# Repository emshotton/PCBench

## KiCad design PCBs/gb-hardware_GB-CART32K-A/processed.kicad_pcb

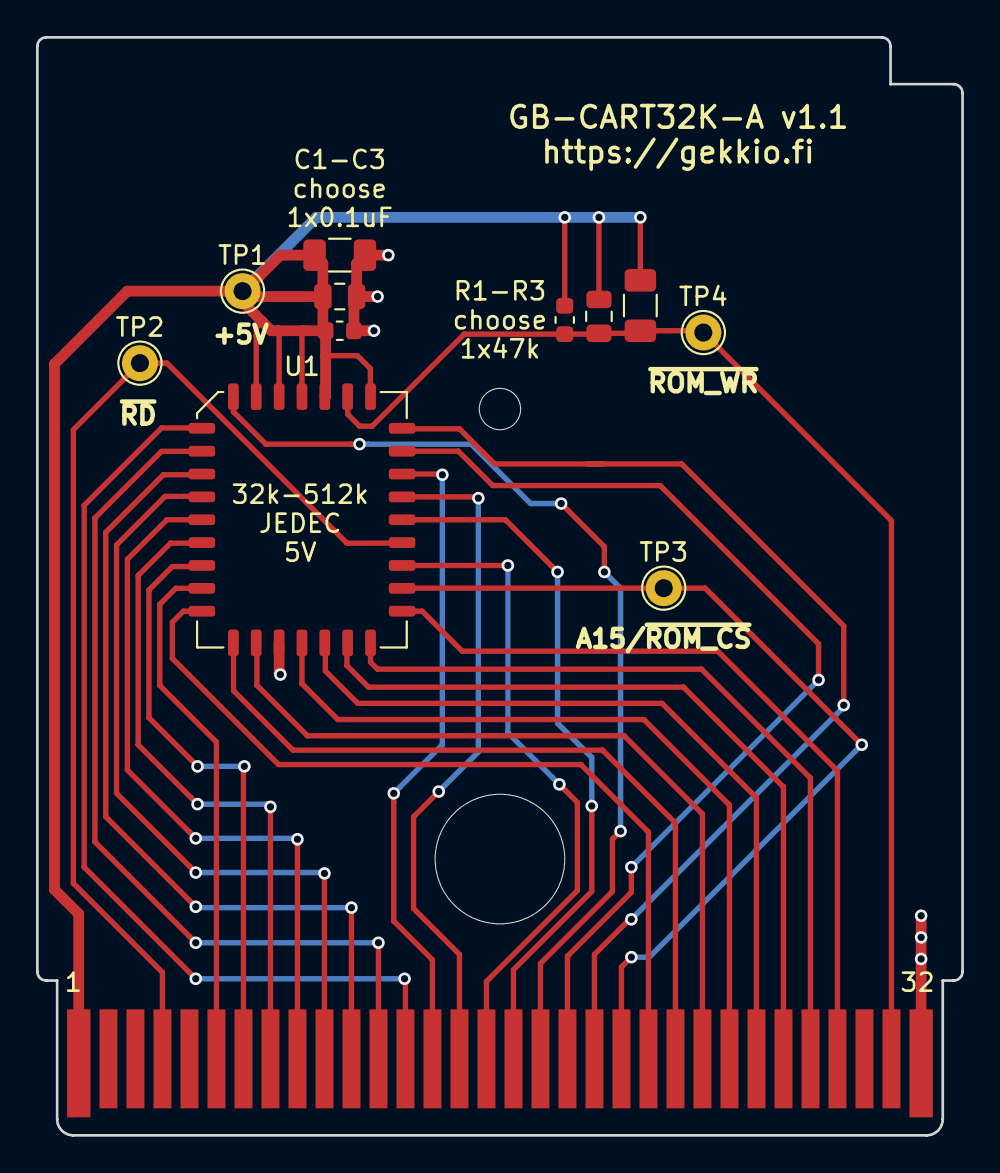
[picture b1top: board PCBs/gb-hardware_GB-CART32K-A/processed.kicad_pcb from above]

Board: 2 copper layers, 51.4 x 61.0 mm, 14 parts (0 on the bottom side), 28 nets.

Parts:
C1: 0.1uF; C_0603_1608Metric
C2: 1uF; C_0805_2012Metric
C3: 10uF; C_1206_3216Metric
H1: DNF; MountingHole_7.2mm
H2: DNF; MountingHole_2.3mm
J1: DNF; GameBoy_Cartridge_1x32_P1.50mm_Edge
R1: 47k; R_0603_1608Metric
R2: 47k; R_0805_2012Metric
R3: 47k; R_1206_3216Metric
TP1, TP2, TP3, TP4: TestPoint; TestPoint_THTPad_D2.0mm_Drill1.0mm
U1: SST39SF040; PLCC-32_11.4x14.0mm_P1.27mm

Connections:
+5V: C1.1, C2.1, C3.1, J1.1, R1.1, R2.1, R3.1, TP1.1, U1.1, U1.2, U1.3, U1.30, U1.32
/A0: J1.6, U1.12
/A1: J1.7, U1.11
/A2: J1.8, U1.10
/A3: J1.9, U1.9
/A4: J1.10, U1.8
/A5: J1.11, U1.7
/A6: J1.12, U1.6
/A7: J1.13, U1.5
/A8: J1.14, U1.27
/A9: J1.15, U1.26
/A10: J1.16, U1.23
/A11: J1.17, U1.25
/A12: J1.18, U1.4
/A13: J1.19, U1.28
/A14: J1.20, U1.29
/D0: J1.22, U1.13
/D1: J1.23, U1.14
/D2: J1.24, U1.15
/D3: J1.25, U1.17
/D4: J1.26, U1.18
/D5: J1.27, U1.19
/D6: J1.28, U1.20
/D7: J1.29, U1.21
/~RD: J1.4, TP2.1, U1.24
/~ROM_CS: J1.21, TP3.1, U1.22
/~ROM_WR: J1.31, R1.2, R2.2, R3.2, TP4.1, U1.31
GND: C1.2, C2.2, C3.2, J1.32, U1.16

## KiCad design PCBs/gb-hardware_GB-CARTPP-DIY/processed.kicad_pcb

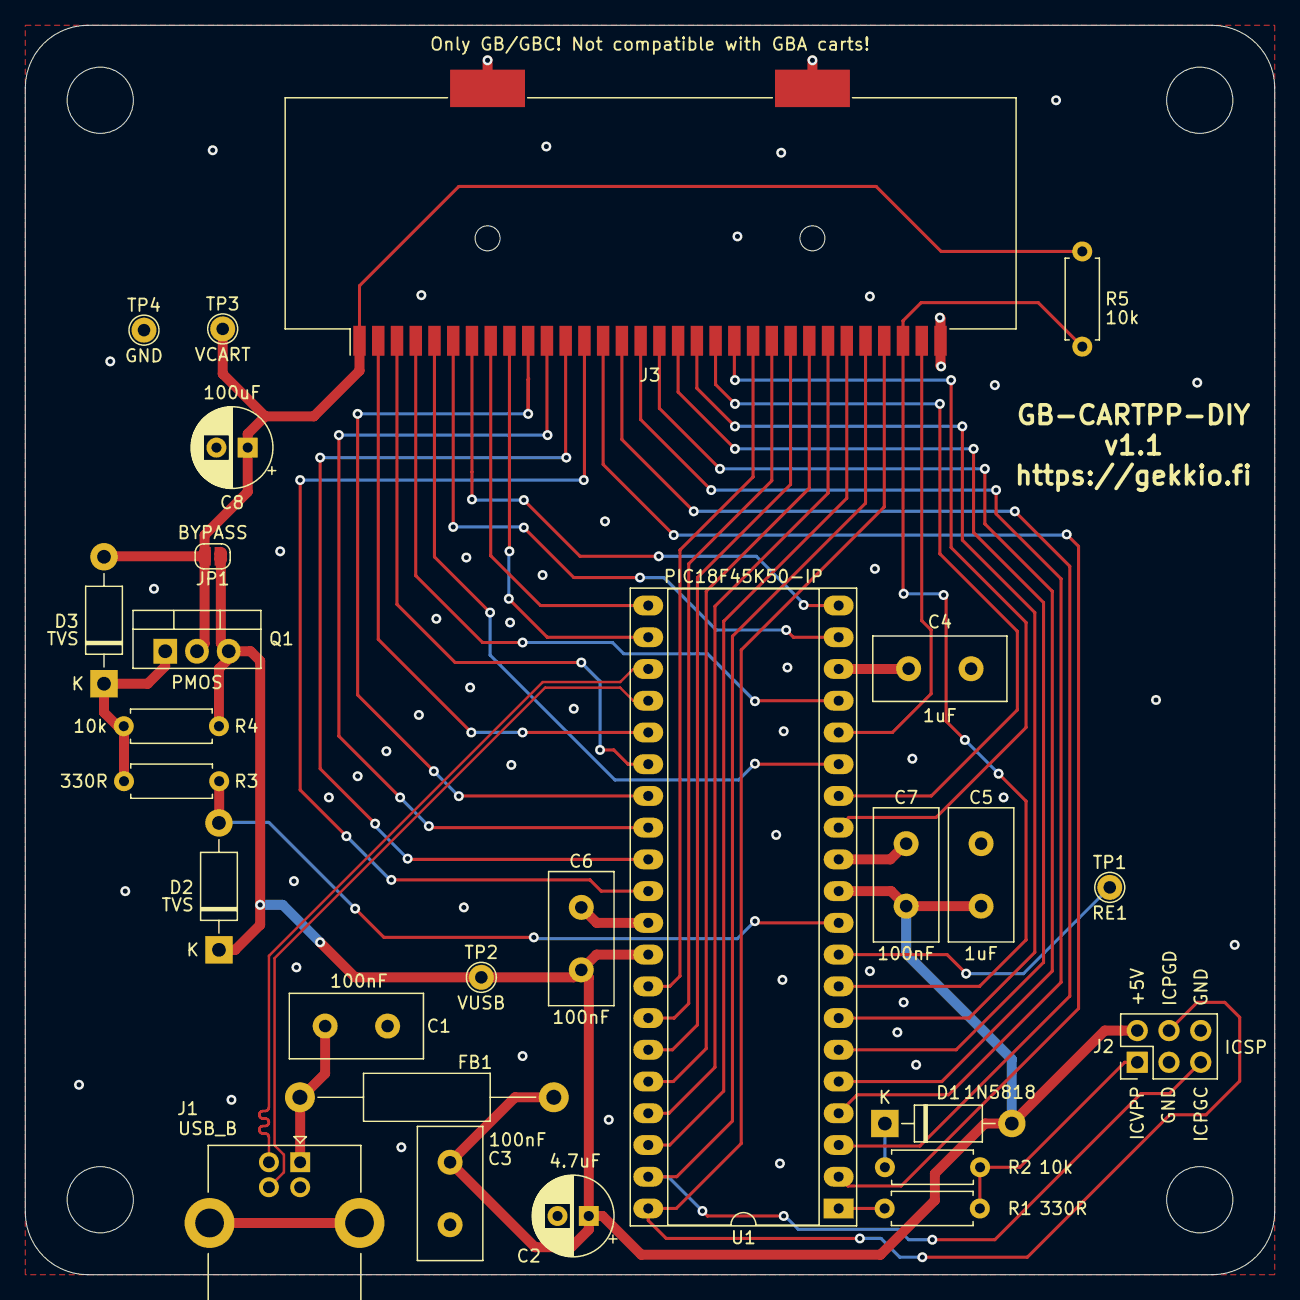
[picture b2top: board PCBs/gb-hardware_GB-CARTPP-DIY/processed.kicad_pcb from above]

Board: 2 copper layers, 100.0 x 100.0 mm, 31 parts (0 on the bottom side), 43 nets.

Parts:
C1, C3, C6, C7: 100nF; C_Disc_D10.5mm_W5.0mm_P5.00mm
C2: 4.7uF; CP_Radial_D6.3mm_P2.50mm
C4, C5: 1uF; C_Disc_D10.5mm_W5.0mm_P5.00mm
C8: 100uF; CP_Radial_D6.3mm_P2.50mm
D1: 1N5818; D_DO-41_SOD81_P10.16mm_Horizontal
D2, D3: TVS; D_DO-41_SOD81_P10.16mm_Horizontal
FB1: Ferrite_Bead_Small; R_Axial_DIN0411_L9.9mm_D3.6mm_P20.32mm_Horizontal
H1, H2, H3, H4: DNP; MountingHole_5.3mm_M5
J1: USB_B; USB_B_Lumberg_2411_02_Horizontal
J2: ICSP; PinHeader_2x03_P2.54mm_Vertical
J3: GameBoy_Cartridge_MountingPin; GameBoy_Cartridge_AGS_1x32-1MP_P1.50mm_Socket_Horizontal
JP1: BYPASS; SolderJumper-2_P1.3mm_Open_RoundedPad1.0x1.5mm
Q1: PMOS; TO-220-3_Vertical
R1, R3: 330R; R_Axial_DIN0207_L6.3mm_D2.5mm_P7.62mm_Horizontal
R2, R4, R5: 10k; R_Axial_DIN0207_L6.3mm_D2.5mm_P7.62mm_Horizontal
TP1: RE1; TestPoint_THTPad_D2.0mm_Drill1.0mm
TP2: VUSB; TestPoint_THTPad_D2.0mm_Drill1.0mm
TP3: VCART; TestPoint_THTPad_D2.0mm_Drill1.0mm
TP4: GND; TestPoint_THTPad_D2.0mm_Drill1.0mm
U1: PIC18F45K50-IP; DIP-40_W15.24mm_Socket_LongPads

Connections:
+5V: C2.1, C3.1, C5.1, C6.1, C7.1, D1.2, D2.1, FB1.1, J2.2, JP1.1, Q1.3, R4.1, TP2.1, U1.11, U1.32
/A0: J3.6, U1.19
/A1: J3.7, U1.20
/A2: J3.8, U1.21
/A3: J3.9, U1.22
/A4: J3.10, U1.27
/A5: J3.11, U1.28
/A6: J3.12, U1.29
/A7: J3.13, U1.30
/A8: J3.14, U1.2
/A9: J3.15, U1.3
/A10: J3.16, U1.4
/A11: J3.17, U1.5
/A12: J3.18, U1.6
/A13: J3.19, U1.7
/A14: J3.20, U1.14
/A15: J3.21, U1.13
/D0: J3.22, U1.33
/D1: J3.23, U1.34
/D2: J3.24, U1.35
/D3: J3.25, U1.36
/D4: J3.26, U1.37
/D5: J3.27, U1.38
/D6: J2.5, J3.28, U1.39
/D7: J2.4, J3.29, U1.40
/ICVPP: J2.1, R1.1, R2.2
/P31: J3.31, U1.16
/PHI: J3.2, U1.25
/USB_N: J1.2, U1.23
/USB_P: J1.3, U1.24
/VCART_EN: D2.2, R3.2, U1.10
/~CS: J3.5, U1.15
/~RD: J3.4, U1.17
/~RES: J3.30, R5.2, U1.8
/~WR: J3.3, U1.26
GND: C1.2, C2.2, C3.2, C4.2, C5.2, C6.2, C7.2, C8.2, J1.4, J2.3, J2.6, J3.32, J3.MP, TP4.1, U1.12, U1.31
unnamed: C1.1, FB1.2, J1.1
unnamed: C4.1, U1.18
unnamed: C8.1, D3.2, J3.1, JP1.2, Q1.2, R5.1, TP3.1
unnamed: D1.1, R2.1
unnamed: D3.1, Q1.1, R3.1, R4.2
unnamed: R1.2, U1.1
unnamed: TP1.1, U1.9

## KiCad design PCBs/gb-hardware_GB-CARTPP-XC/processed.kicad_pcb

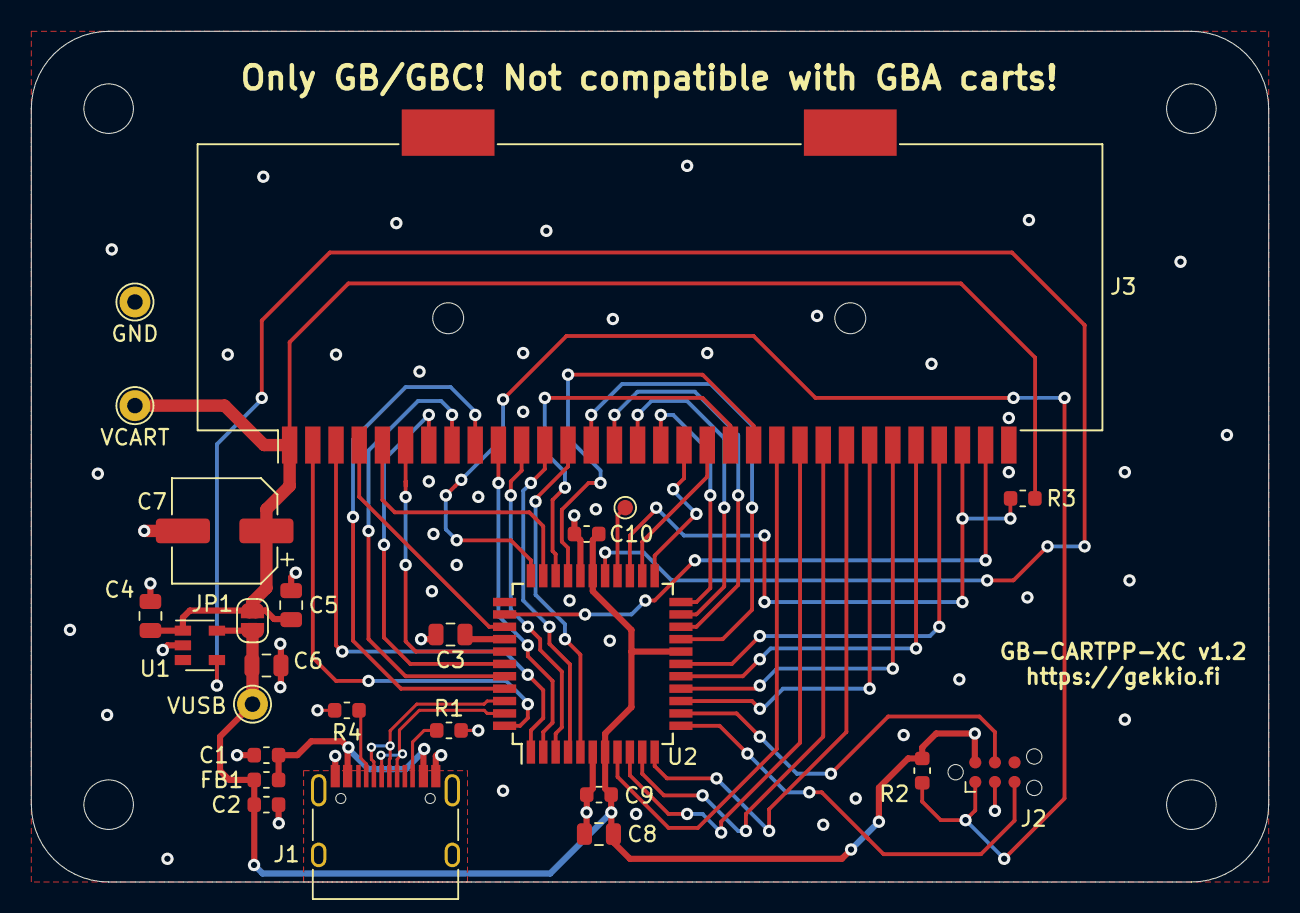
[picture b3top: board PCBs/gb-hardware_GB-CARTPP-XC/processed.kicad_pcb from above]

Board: 2 copper layers, 80.0 x 55.0 mm, 29 parts (0 on the bottom side), 44 nets.

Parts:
C1, C2, C9, C10: 100nF; C_0603_1608Metric
C3, C8: 1uF; C_0805_2012Metric
C4, C5, C6: 4.7uF; C_0805_2012Metric
C7: 100uF; CP_Elec_6.3x5.8
FB1: MPZ1608S331; L_0603_1608Metric
H1, H2, H3, H4: DNP; MountingHole_3.2mm_M3
J1: TYPE-C-31-M-12; USB_C_Receptacle_HRO_TYPE-C-31-M-12
J2: DNP; Tag-Connect_TC2030-IDC-NL_2x03_P1.27mm_Vertical
J3: GameBoy_Cartridge_MountingPin; GameBoy_Cartridge_AGS_1x32-1MP_P1.50mm_Socket_Horizontal
JP1: BYPASS; SolderJumper-2_P1.3mm_Open_RoundedPad1.0x1.5mm
R1, R4: 5k1; R_0603_1608Metric
R2, R3: 10k; R_0603_1608Metric
TP1: VUSB; TestPoint_THTPad_D2.0mm_Drill1.0mm
TP2: RE1; TestPoint_Pad_D1.0mm
TP3: VCART; TestPoint_THTPad_D2.0mm_Drill1.0mm
TP4: GND; TestPoint_THTPad_D2.0mm_Drill1.0mm
U1: SY6288AAAC; SOT-23-5
U2: PIC18F45K50_QFP; TQFP-44_10x10mm_P0.8mm

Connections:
+5V: C2.1, C6.1, C8.1, C9.1, C10.1, FB1.2, J2.2, JP1.1, R2.1, TP1.1, U1.5, U2.7, U2.18, U2.28
/A0: J3.6, U2.38
/A1: J3.7, U2.39
/A2: J3.8, U2.40
/A3: J3.9, U2.41
/A4: J3.10, U2.2
/A5: J3.11, U2.3
/A6: J3.12, U2.4
/A7: J3.13, U2.5
/A8: J3.14, U2.19
/A9: J3.15, U2.20
/A10: J3.16, U2.21
/A11: J3.17, U2.22
/A12: J3.18, U2.23
/A13: J3.19, U2.24
/A14: J3.20, U2.31
/A15: J3.21, U2.30
/D0: J3.22, U2.8
/D1: J3.23, U2.9
/D2: J3.24, U2.10
/D3: J3.25, U2.11
/D4: J3.26, U2.14
/D5: J3.27, U2.15
/D6: J3.28, U2.16
/D7: J3.29, U2.17
/PGC: J2.5, U2.12
/PGD: J2.4, U2.13
/PHI: J3.2, U2.44
/TP_RE1: TP2.1, U2.26
/USB_N: J1.A7, J1.B7, U2.42
/USB_P: J1.A6, J1.B6, U2.43
/VPP: J2.1, R2.2, U2.33
/~CS: J3.5, U2.32
/~P31: J3.31, U2.35
/~RD: J3.4, U2.36
/~RES: J3.30, R3.2, U2.25
/~WR: J3.3, U2.1
GND: C1.2, C2.2, C3.2, C4.2, C5.2, C6.2, C7.2, C8.2, C9.2, C10.2, J1.A1, J1.A12, J1.B1, J1.B12, J2.3, J3.32, J3.MP, R1.2, R4.2, TP4.1, U1.2, U2.6, U2.29
unnamed: C1.1, FB1.1, J1.A4, J1.A9, J1.B4, J1.B9
unnamed: C3.1, U2.37
unnamed: J1.A5, R4.1
unnamed: J1.B5, R1.1
unnamed: U1.4, U2.27
VCART: C4.1, C5.1, C7.1, J3.1, JP1.2, R3.1, TP3.1, U1.1

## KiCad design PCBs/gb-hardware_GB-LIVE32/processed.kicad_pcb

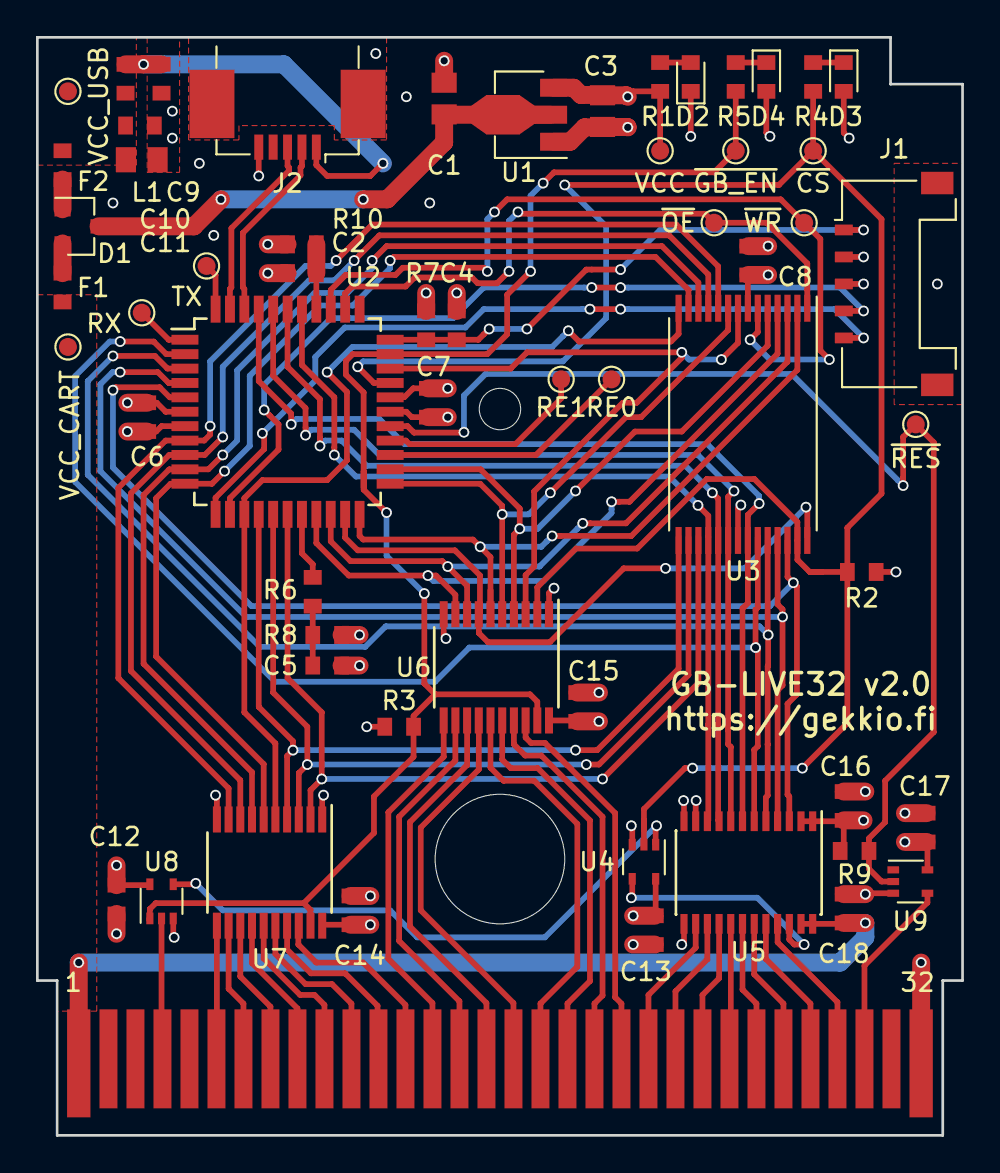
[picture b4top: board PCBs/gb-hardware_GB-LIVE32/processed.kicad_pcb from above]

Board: 4 copper layers, 51.4 x 61.0 mm, 61 parts (0 on the bottom side), 79 nets.

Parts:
C1, C3, C11: 4.7uF; C_0805_2012Metric
C2: 0.47uF; C_0603_1608Metric
C4, C5, C6, C7, C8, C9, C10, C12, C13, C14, C15, C16, C17, C18: 0.1uF; C_0603_1608Metric
D1: BAT54C; SOT-23
D2: LED_R; LED_0603_1608Metric
D3, D4: LED_Y; LED_0603_1608Metric
F1, F2: Fuse; Fuse_0603_1608Metric
J1: Conn_01x05; Molex_Pico-Lock_504050-0591_1x05-1MP_P1.50mm_Horizontal
J2: USB_B_Mini; USB_Mini-B_Hirose_UX60SC-MB-5ST80_Horizontal
J3: DNF; GameBoy_Cartridge_1x32_P1.50mm_Edge
L1: Ferrite_Bead; L_0603_1608Metric
MK1: Mounting_Hole; MountingHole_7.2mm
MK2: Mounting_Hole; MountingHole_2.3mm
R1, R4, R5: 3.3k; R_0603_1608Metric
R2, R3, R7, R8, R9: 10k; R_0603_1608Metric
R6: 470; R_0603_1608Metric
R10: 0; R_0603_1608Metric
TP1: VCC_CART; TestPoint_Pad_D1.0mm
TP2: RE0; TestPoint_Pad_D1.0mm
TP3: RE1; TestPoint_Pad_D1.0mm
TP4: TX; TestPoint_Pad_D1.0mm
TP5: RX; TestPoint_Pad_D1.0mm
TP6: VCC; TestPoint_Pad_D1.0mm
TP7: ~{CS}; TestPoint_Pad_D1.0mm
TP8: ~{GB_EN}; TestPoint_Pad_D1.0mm
TP9: ~{WR}; TestPoint_Pad_D1.0mm
TP10: ~{OE}; TestPoint_Pad_D1.0mm
TP11: VCC_USB; TestPoint_Pad_D1.0mm
TP12: ~{RES}; TestPoint_Pad_D1.0mm
U1: MCP1703A-3302_SOT89; SOT-89-3
U2: PIC18LF45K50_QFP; TQFP-44_10x10mm_P0.8mm
U3: IS61LV256AL-10T; TSOP-I-28_11.8x8mm_P0.55mm_Pin1Middle
U4, U8: 74LVC1G32; SOT-353_SC-70-5
U5: 74LVC8T245PW; TSSOP-24_4.4x7.8mm_P0.65mm
U6, U7: 74LVC245APW; TSSOP-20_4.4x6.5mm_P0.65mm
U9: 74LVC1G07; SOT-353_SC-70-5

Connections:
/A0: U2.8, U3.3, U7.9
/A1: U2.9, U3.4, U7.8
/A2: U2.10, U3.5, U7.7
/A3: U2.11, U3.6, U7.6
/A4: U2.14, U3.7, U7.5
/A5: U2.15, U3.8, U7.4
/A6: U2.16, U3.9, U7.3
/A7: U2.17, U3.10, U7.2
/A8: U2.19, U3.25, U6.9
/A9: U2.20, U3.24, U6.8
/A10: U2.21, U3.21, U6.7
/A11: U2.22, U3.23, U6.6
/A12: U2.23, U3.2, U6.5
/A13: U2.24, U3.26, U6.4
/A14: U2.31, U3.1, U6.3
/D0: U2.38, U3.11, U5.10
/D1: U2.39, U3.12, U5.9
/D2: U2.40, U3.13, U5.8
/D3: U2.41, U3.15, U5.7
/D4: U2.2, U3.16, U5.6
/D5: U2.3, U3.17, U5.5
/D6: U2.4, U3.18, U5.4
/D7: U2.5, U3.19, U5.3
/PGC: J1.5, U2.12
/PGD: J1.4, U2.13
/USB_N: J2.2, U2.42
/USB_P: J2.3, U2.43
/VCC_CART: C18.1, F1.2, J3.1, TP1.1, U5.23, U5.24
/VCC_USB: C10.1, C11.2, F2.2, L1.1, TP11.1
/VPP: C4.2, J1.1, R7.2, U2.33
/gameboy/GB_A0: J3.6, U7.11
/gameboy/GB_A1: J3.7, U7.12
/gameboy/GB_A2: J3.8, U7.13
/gameboy/GB_A3: J3.9, U7.14
/gameboy/GB_A4: J3.10, U7.15
/gameboy/GB_A5: J3.11, U7.16
/gameboy/GB_A6: J3.12, U7.17
/gameboy/GB_A7: J3.13, U7.18
/gameboy/GB_A8: J3.14, U6.11
/gameboy/GB_A9: J3.15, U6.12
/gameboy/GB_A10: J3.16, U6.13
/gameboy/GB_A11: J3.17, U6.14
/gameboy/GB_A12: J3.18, U6.15
/gameboy/GB_A13: J3.19, U6.16
/gameboy/GB_A14: J3.20, U6.17
/gameboy/GB_A15: J3.21, U6.18
/gameboy/GB_D0: J3.22, U5.14
/gameboy/GB_D1: J3.23, U5.15
/gameboy/GB_D2: J3.24, U5.16
/gameboy/GB_D3: J3.25, U5.17
/gameboy/GB_D4: J3.26, U5.18
/gameboy/GB_D5: J3.27, U5.19
/gameboy/GB_D6: J3.28, U5.20
/gameboy/GB_D7: J3.29, U5.21
/gameboy/~GB_RD: J3.4, U8.2
/gameboy/~GB_RES: J3.30, U9.4
/~CS: R2.2, R4.1, TP7.1, U2.30, U3.20, U4.2, U6.2
/~GB_EN: R3.2, R5.1, TP8.1, U2.32, U6.19, U7.19, U8.1
/~GB_RES: R9.2, TP12.1, U2.27, U9.2
/~OE: TP10.1, U2.35, U3.22
/~WR: TP9.1, U2.36, U3.27
GND: C1.1, C2.2, C3.1, C4.1, C5.1, C6.2, C7.2, C8.2, C9.2, C10.2, C11.1, C12.2, C13.2, C14.2, C15.2, C16.2, C17.2, C18.2, D2.1, J1.3, J1.MP, J2.5, J2.6, J3.32, U1.1, U2.6, U2.29, U3.14, U4.3, U5.11, U5.12, U5.13, U6.1, U6.10, U7.1, U7.10, U8.3, U9.3
unnamed: C1.2, D1.3, U1.2
unnamed: C2.1, R10.2, U2.37
unnamed: C5.2, R6.2, R8.2
unnamed: C9.1, J2.1, L1.2
unnamed: D1.1, F2.1
unnamed: D1.2, F1.1
unnamed: D2.2, R1.2
unnamed: D3.1, R4.2
unnamed: D4.1, R5.2
unnamed: R6.1, U2.18
unnamed: TP2.1, U2.25
unnamed: TP3.1, U2.26
unnamed: TP4.1, U2.44
unnamed: TP5.1, U2.1
unnamed: U4.1, U8.4
unnamed: U4.4, U5.22
VCC: C3.2, C6.1, C7.1, C8.1, C12.1, C13.1, C14.1, C15.1, C16.1, C17.1, D3.2, D4.2, J1.2, R1.1, R2.1, R3.1, R7.1, R8.1, R9.1, R10.1, TP6.1, U1.3, U2.7, U2.28, U3.28, U4.5, U5.1, U5.2, U6.20, U7.20, U8.5, U9.5

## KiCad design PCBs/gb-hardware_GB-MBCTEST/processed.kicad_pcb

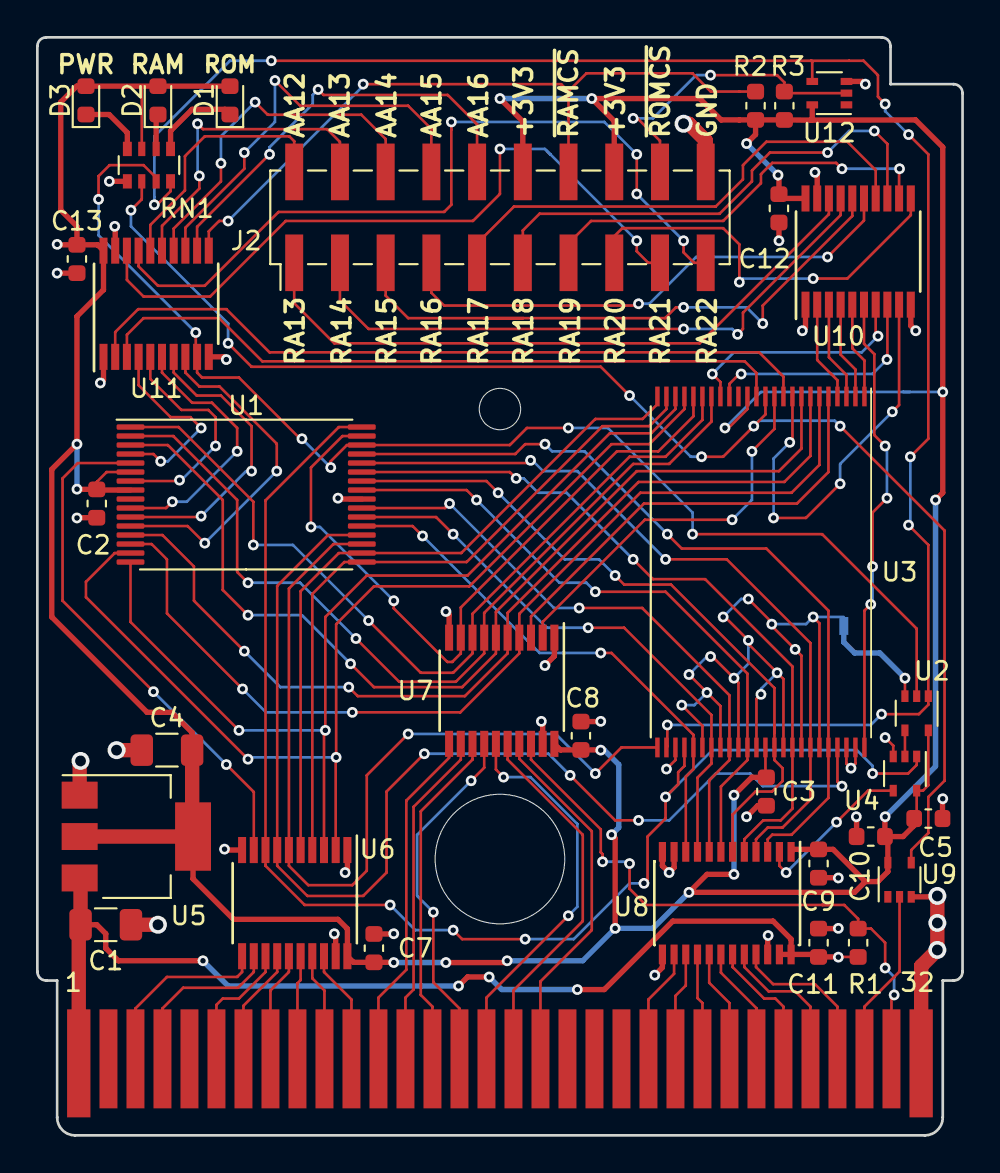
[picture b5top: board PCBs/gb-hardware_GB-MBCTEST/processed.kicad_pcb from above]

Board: 2 copper layers, 51.4 x 61.0 mm, 36 parts (1 on the bottom side), 93 nets.

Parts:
C1, C4: 10uF; C_1206_3216Metric
C2, C3, C5, C7, C8, C9, C10, C11, C12, C13: 100nF; C_0603_1608Metric
D1, D2: LED_Y; LED_0603_1608Metric
D3: LED_R; LED_0603_1608Metric
H1: DNF; MountingHole_7.2mm
H2: DNF; MountingHole_2.3mm
J1: DNF; GameBoy_Cartridge_1x32_P1.50mm_Edge
J2: Conn_02x10_Odd_Even; PinHeader_2x10_P2.54mm_Vertical_SMD
NT1: Net-Tie_2; NetTie-2_SMD_Pad0.5mm
R1: 49k; R_0603_1608Metric
R2, R3: 100k; R_0603_1608Metric
RN1: 4.7k; R_Array_Convex_4x0603
U1: IS62WV1288DBLL-45H; TSOP-I-32_11.8x8mm_P0.5mm
U2: 74LVC1G08; SOT-353_SC-70-5
U3: MX29LV640ExT; TSOP-I-48_18.4x12mm_P0.5mm
U4: 74LVC1G02; SOT-353_SC-70-5
U5: AP2114H-3.3; SOT-223
U6, U7: 74LVC245APW; TSSOP-20_4.4x6.5mm_P0.65mm
U8: 74LVC8T245PW; TSSOP-24_4.4x7.8mm_P0.65mm
U9: 74LVC1G07; SOT-353_SC-70-5
U10, U11: 74LVCH245APW; TSSOP-20_4.4x6.5mm_P0.65mm
U12: 74LVC1G17; SOT-353_SC-70-5

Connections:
+3V3: C2.1, C3.1, C4.1, C5.1, C7.1, C8.1, C9.1, C10.1, C12.1, C13.1, D1.2, D2.2, D3.2, J2.12, J2.16, R2.1, R3.1, RN1.7, U1.6, U1.8, U2.5, U3.14, U3.37, U4.5, U5.2, U5.4, U6.20, U7.20, U8.1, U9.5, U10.20, U11.20, U12.5
+5V: C1.1, C11.1, J1.1, R1.1, U5.3, U8.23, U8.24
/A0: U1.20, U3.45, U6.7
/A1: U1.19, U3.25, U6.6
/A2: U1.18, U3.24, U6.5
/A3: U1.17, U3.23, U6.4
/A4: U1.16, U3.22, U6.3
/A5: U1.15, U3.21, U6.2
/A6: U1.31, U3.20, U7.9
/A7: U1.1, U3.19, U7.8
/A8: U1.2, U3.18, U7.7
/A9: U1.3, U3.8, U7.6
/A10: U1.13, U3.7, U7.5
/A11: U1.14, U3.6, U7.4
/A12: U3.5, U7.3
/D0: U1.21, U3.29, U8.10
/D1: U1.22, U3.31, U8.9
/D2: U1.23, U3.33, U8.8
/D3: U1.25, U3.35, U8.7
/D4: U1.26, U3.38, U8.6
/D5: U1.27, U3.40, U8.5
/D6: U1.28, U3.42, U8.4
/D7: U1.29, U3.44, U8.3
/DATA_DIR: U4.4, U8.2
/Game Boy Cartridge/GB_A0: J1.6, U6.13
/Game Boy Cartridge/GB_A1: J1.7, U6.14
/Game Boy Cartridge/GB_A2: J1.8, U6.15
/Game Boy Cartridge/GB_A3: J1.9, U6.16
/Game Boy Cartridge/GB_A4: J1.10, U6.17
/Game Boy Cartridge/GB_A5: J1.11, U6.18
/Game Boy Cartridge/GB_A6: J1.12, U7.11
/Game Boy Cartridge/GB_A7: J1.13, U7.12
/Game Boy Cartridge/GB_A8: J1.14, U7.13
/Game Boy Cartridge/GB_A9: J1.15, U7.14
/Game Boy Cartridge/GB_A10: J1.16, U7.15
/Game Boy Cartridge/GB_A11: J1.17, U7.16
/Game Boy Cartridge/GB_A12: J1.18, U7.17
/Game Boy Cartridge/GB_D0: J1.22, U8.14
/Game Boy Cartridge/GB_D1: J1.23, U8.15
/Game Boy Cartridge/GB_D2: J1.24, U8.16
/Game Boy Cartridge/GB_D3: J1.25, U8.17
/Game Boy Cartridge/GB_D4: J1.26, U8.18
/Game Boy Cartridge/GB_D5: J1.27, U8.19
/Game Boy Cartridge/GB_D6: J1.28, U8.20
/Game Boy Cartridge/GB_D7: J1.29, U8.21
/Game Boy Cartridge/GB_VIN: J1.31, R1.2, U7.18
/Game Boy Cartridge/~GB_RD: J1.4, U6.12
/Game Boy Cartridge/~GB_WR: J1.3, U6.11
/MBC/MBC_RAM_A12: J2.2, U11.16
/MBC/MBC_RAM_A13: J2.4, U11.15
/MBC/MBC_RAM_A14: J2.6, U11.14
/MBC/MBC_RAM_A15: J2.8, U11.13
/MBC/MBC_RAM_A16: J2.10, U11.12
/MBC/MBC_ROM_A13: J2.1, U10.18
/MBC/MBC_ROM_A14: J2.3, U10.17
/MBC/MBC_ROM_A15: J2.5, U10.16
/MBC/MBC_ROM_A16: J2.7, U10.15
/MBC/MBC_ROM_A17: J2.9, U10.14
/MBC/MBC_ROM_A18: J2.11, U10.13
/MBC/MBC_ROM_A19: J2.13, U10.12
/MBC/MBC_ROM_A20: J2.15, U10.11
/MBC/MBC_ROM_A21: J2.17, U11.18
/MBC/MBC_ROM_A22: J2.19, U11.17
/MBC/~MBC_RAM_CS: J2.14, R2.2, U11.11
/MBC/~MBC_ROM_CS: J2.18, R3.2, U12.2
/RAM_A12: U1.4, U11.4
/RAM_A13: U1.7, U11.5
/RAM_A14: U1.10, U11.6
/RAM_A15: U1.11, U11.7
/RAM_A16: U1.12, U11.8
/ROM_A13: U3.4, U10.2
/ROM_A14: U3.3, U10.3
/ROM_A15: U3.2, U10.4
/ROM_A16: U3.1, U10.5
/ROM_A17: U3.48, U10.6
/ROM_A18: U3.17, U10.7
/ROM_A19: U3.16, U10.8
/ROM_A20: U3.9, U10.9
/ROM_A21: U3.10, U11.2
/ROM_A22: U3.13, U11.3
/~RAM_CS: RN1.3, U1.30, U2.2, U11.9
/~RAM_WR: U1.5, U6.9
/~RD: U1.32, U3.28, U4.1, U6.8
/~RESET: RN1.2, U3.12, U9.4
/~ROM_CS: RN1.4, U2.1, U3.26, U12.4
/~ROM_WR: U3.11, U7.2
GND: C1.2, C2.2, C3.2, C4.2, C5.2, C7.2, C8.2, C9.2, C10.2, C11.2, C12.2, C13.2, J1.32, J2.20, NT1.2, RN1.1, U1.24, U2.3, U3.27, U3.46, U3.47, U4.3, U5.1, U6.1, U6.10, U6.19, U7.1, U7.10, U7.19, U8.11, U8.12, U8.13, U8.22, U9.3, U10.1, U10.10, U10.19, U11.1, U11.10, U11.19, U12.3
unnamed: D1.1, RN1.5
unnamed: D2.1, RN1.6
unnamed: D3.1, RN1.8
unnamed: J1.30, U9.2
unnamed: NT1.1, U3.30, U3.32, U3.34, U3.36, U3.39, U3.41, U3.43
unnamed: U2.4, U4.2

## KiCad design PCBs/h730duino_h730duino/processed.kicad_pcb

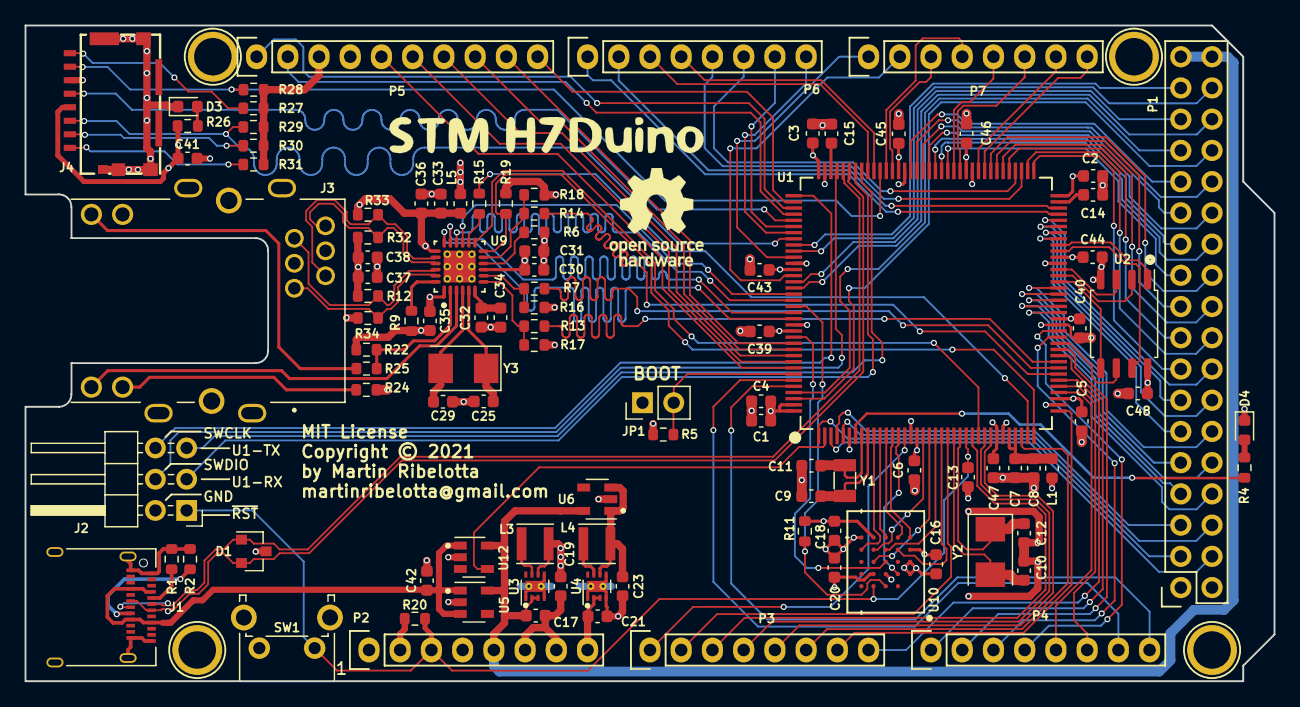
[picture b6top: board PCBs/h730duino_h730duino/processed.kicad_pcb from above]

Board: 4 copper layers, 101.6 x 53.3 mm, 111 parts (1 on the bottom side), 152 nets.

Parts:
C1: 4.7u; C_0603_1608Metric
C2, C3, C4, C5, C6, C7, C16, C18, C20, C31, C33, C35, C39, C40, C41, C43, C44, C45, C46, C47, C48: 100n; C_0603_1608Metric
C8, C9, C11, C25, C29: 10p; C_0603_1608Metric
C10, C12: 20p; C_0603_1608Metric
C13, C34: 1u; C_0603_1608Metric
C14, C15, C42: 2.2u; C_0603_1608Metric
C17, C21, C30, C36: 10u; C_0603_1608Metric
C19, C23: 22u; C_0603_1608Metric
C32: 470p; C_0603_1608Metric
C37, C38: 0.022u; C_0603_1608Metric
D1: SP0502BAHT; SOT-23
D3, D4: LEDRED; LED_0603_1608Metric
G1: LOGO; logo
J1: USB_C_Receptacle_USB2.0; USB_C_Receptacle_Amphenol_12401610E4-2A
J2: Conn_02x03_Odd_Even; PinHeader_2x03_P2.54mm_Horizontal
J3: L834-1G1T-91; BEL_L834-1G1T-91
J4: 105162-0001
JP1: BOOT; PinHeader_1x02_P2.54mm_Vertical
L1, L5: ferrite; L_0603_1608Metric
L3, L4: NR3015T2R2M; L_Taiyo-Yuden_MD-3030
LOGO1: Logo_Open_Hardware_Small; OSHW-Logo_7.5x8mm_SilkScreen
P1: CONN_02x18; Socket_Strip_Arduino_2x18
P2, P3, P4, P6, P7: CONN_01x08; Socket_Strip_Arduino_1x08
P5: CONN_01x10; Socket_Strip_Arduino_1x10
P8, P10, P11, P13: CONN_01X01; Arduino_1pin
QR1: https://github.com/martinribelotta/h730duino; url_qr
R1, R2, R4, R19, R26: 1K5; R_0603_1608Metric
R5, R6, R7, R11, R13, R14, R15, R16, R17, R18, R20, R22, R27, R28, R29, R30, R31: 10K; R_0603_1608Metric
R9: 12.1K 1%; R_0603_1608Metric
R12, R32, R33, R34: 49.9R; R_0603_1608Metric
R24, R25: 220R; R_0603_1608Metric
SW1: RESET; SW_Tactile_SPST_Angled_PTS645Vx39-2LFS
U1: STM32H730ZBT6
U2: IS25LP032D-JBLE-TR; SOIC-8_5.23x5.23mm_P1.27mm
U3: TPS62162DSG; WSON-8-1EP_2x2mm_P0.5mm_EP0.9x1.6mm_ThermalVias
U4: TPS62163DSG; WSON-8-1EP_2x2mm_P0.5mm_EP0.9x1.6mm_ThermalVias
U5, U6: MAX40200AUK; SOT-23-5
U9: LAN8742A; Microchip-C04-143B-S4QFN-0-0-MFG
U10: S27KL0641DABHI020
U12: AP2161W; SOT-23-5
Y1: 32.768K; Crystal_SMD_3215-2Pin_3.2x1.5mm
Y2: 8M; Crystal_SMD_5032-2Pin_5.0x3.2mm
Y3: 25M; Crystal_SMD_5032-2Pin_5.0x3.2mm

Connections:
+3V3: C1.1, C2.1, C3.1, C4.1, C5.1, C6.1, C16.1, C18.1, C19.1, C20.1, C30.1, C31.1, C39.1, C40.1, C41.1, C43.1, C44.1, C45.1, C46.1, C47.1, C48.1, J4.4, JP1.1, L1.1, L3.2, L5.1, P2.2, P2.4, P5.3, R11.1, R16.1, R17.1, R18.1, R19.1, R20.2, R26.2, R27.1, R28.1, R29.1, R30.1, R31.1, U1.6, U1.17, U1.30, U1.39, U1.52, U1.62, U1.72, U1.84, U1.95, U1.108, U1.121, U1.131, U1.143, U1.144, U2.8, U3.6, U9.9, U10.B4, U10.D1, U10.E4
+5V: C17.1, P1.35, P1.36, P2.5, U3.2, U3.3, U5.5, U6.5, U12.5
/0(Rx0): P6.8, U1.115
/1(Tx0): P6.7, U1.114
/2(**): P6.6, U1.76
/3(**): P6.5, U1.75
/4(**): P6.4, U1.99
/5(**): P6.3, U1.100
/5Vreg: C23.1, L4.2, U4.6, U6.1, U6.3
/6(**): P6.2, U1.70
/7(**): P6.1, U1.69
/8(**): P5.10, U1.110
/9(**): P5.9, U1.133
/10(**): P5.8, U1.134
/11(**): P5.7, U1.135
/12(**): P5.6, U1.136
/13(**): P5.5, U1.137
/14(Tx3): P7.1, U1.119
/15(Rx3): P7.2, U1.122
/16(Tx2): P7.3, U1.96
/17(Rx2): P7.4, U1.97
/18(Tx1): P7.5, U1.86
/19(Rx1): P7.6, U1.85
/20(SDA): P7.7, U1.82
/21(SCL): P7.8, U1.81
/22: P1.33, U1.117
/23: P1.34, U1.118
/24: P1.31, U1.123
/25: P1.32, U1.124
/26: P1.29, U1.141
/27: P1.30, U1.142
/28: P1.27, U1.93
/29: P1.28, U1.92
/30: P1.25, U1.91
/31: P1.26, U1.90
/32: P1.23, U1.89
/33: P1.24, U1.88
/34: P1.21, U1.87
/35: P1.22, U1.80
/36: P1.19, U1.79
/37: P1.20, U1.78
/38: P1.17, U1.77
/39: P1.18, U1.74
/40: P1.15, U1.73
/41: P1.16, U1.68
/42: P1.13, U1.67
/43: P1.14, U1.66
/44: P1.11, U1.65
/45: P1.12, U1.57
/46: P1.9, U1.56
/47: P1.10, U1.55
/48: P1.7, U1.54
/49: P1.8, U1.53
/50(MISO): P1.5, U1.4
/51(MOSI): P1.6, U1.5
/52(SCK): P1.3, U1.1
/53(SS): P1.4, U1.3
/A0: P3.1, U1.15
/A1: P3.2, U1.22
/A2: P3.3, U1.26
/A3: P3.4, U1.28
/A4: P3.5, U1.29
/A5: P3.6, U1.34
/A6: P3.7, U1.37
/A7: P3.8, U1.42
/A8: P4.1, U1.46
/A9: P4.2, U1.47
/A10: P4.3, U1.49
/A11: P4.4, U1.50
/A12_DAC0: P4.5, U1.40
/A13_DAC1: P4.6, U1.41
/BOOT0: JP1.2, R5.2, U1.138
/CANRX: P4.7, U1.139
/CANTX: P4.8, U1.140
/ETH_CRS_DV: R14.2, U1.43
/ETH_MDC: U1.27, U9.13
/ETH_MDIO: R19.2, U1.36, U9.12
/ETH_REF_CLK: R15.2, U1.35
/ETH_RXD0: R7.2, U1.44
/ETH_RXD1: R13.2, U1.45
/ETH_TXD0: U1.128, U9.17
/ETH_TXD1: U1.129, U9.18
/ETH_TX_EN: U1.126, U9.16
/Ethernet/LED1: J3.14, U9.3
/Ethernet/LED2: R22.2, R25.1, U9.2
/Ethernet/RX_N: J3.6, R12.2, U9.22
/Ethernet/RX_P: J3.4, R34.2, U9.23
/Ethernet/TX_N: J3.10, R33.2, U9.20
/Ethernet/TX_P: J3.12, R32.2, U9.21
/I2C5_SCL: P5.2, U1.112
/I2C5_SDA: P5.1, U1.111
/OCTOSPIM_P1_CLK: U1.48, U2.6
/OCTOSPIM_P1_IO0: U1.20, U10.D3
/OCTOSPIM_P1_IO1: U1.21, U10.D2
/OCTOSPIM_P1_IO2: U1.19, U10.C4
/OCTOSPIM_P1_IO3: U1.18, U10.D4
/OCTOSPIM_P1_IO4: U1.58, U2.5
/OCTOSPIM_P1_IO5: U1.59, U2.2
/OCTOSPIM_P1_IO6: U1.60, U2.3
/OCTOSPIM_P1_IO7: U1.63, U2.7
/OCTOSPIM_P1_NCS: U1.64, U2.1
/OCTOSPIM_P2_CLK: U1.14, U10.B2
/OCTOSPIM_P2_DQS: U1.132, U10.C3
/OCTOSPIM_P2_IO0: U1.10, U10.D5
/OCTOSPIM_P2_IO1: U1.11, U10.E3
/OCTOSPIM_P2_IO2: U1.12, U10.E2
/OCTOSPIM_P2_IO3: U1.13, U10.E1
/OCTOSPIM_P2_NCS: R11.2, U1.127, U10.A3
/SDMMC1_CK: J4.5, U1.113
/SDMMC1_CMD: J4.3, R29.2, U1.116
/SDMMC1_D0: J4.7, R28.2, U1.98
/SWCLK: J2.6, U1.109
/SWDIO: J2.4, U1.105
/USART1_RX: J2.3, U1.102
/USART1_TX: J2.5, U1.101
/USB_OTG_HS_N: D1.2, J1.A7, J1.B7, U1.103
/USB_OTG_HS_P: D1.1, J1.A6, J1.B6, U1.104
/USR_LED: R4.2, U1.7
/Vin: C21.1, P2.8, U4.2, U4.3
/~ETH_RST: U1.125, U9.15
/~RST: C13.1, J2.1, P2.3, R20.1, SW1.1, U1.25, U10.A4
/~USB_ON: U1.2, U12.4
GND: C1.2, C2.2, C3.2, C4.2, C5.2, C6.2, C7.2, C8.2, C9.1, C10.2, C11.1, C12.2, C13.2, C14.2, C15.2, C16.2, C17.2, C18.2, C19.2, C20.2, C21.2, C23.2, C25.1, C29.1, C30.2, C31.2, C32.2, C33.2, C34.2, C35.2, C36.2, C37.2, C38.2, C39.2, C40.2, C41.2, C42.2, C43.2, C44.2, C45.2, C46.2, C47.2, C48.2, D1.3, D3.1, D4.1, J1.A1, J1.A12, J1.B1, J1.B12, J1.S1, J2.2, J3.15, J3.S1, J3.S2, J4.6, J4.9, J4.10, J4.11, J4.12, J4.13, P1.1, P1.2, P2.6, P2.7, P5.4, R1.1, R2.1, R5.1, R6.1, R9.2, R22.1, R24.1, SW1.2, U1.16, U1.31, U1.38, U1.51, U1.61, U1.83, U1.94, U1.107, U1.120, U1.130, U2.4, U3.1, U3.4, U3.5, U3.9, U4.1, U4.4, U4.5, U4.9, U5.2, U6.2, U9.25, U10.B1, U10.B3, U10.C1, U10.E5, U12.2
unnamed: C9.2, U1.9, Y1.1
unnamed: C10.1, U1.23, Y2.2
unnamed: C11.2, U1.8, Y1.2
unnamed: C12.1, U1.24, Y2.1
unnamed: C14.1, U1.71
unnamed: C15.1, U1.106
unnamed: C25.2, U9.5, Y3.1
unnamed: C29.2, U9.4, Y3.2
unnamed: C32.1, C34.1, U9.6
unnamed: C33.1, C35.1, C36.1, C37.1, C38.1, J3.5, J3.11, L5.2, R12.1, R32.1, R33.1, R34.1, U9.1, U9.19
unnamed: D3.2, R26.1
unnamed: D4.2, R4.1
unnamed: J1.A5, R1.2
unnamed: J1.B5, R2.2
unnamed: J3.13, R24.2
unnamed: J3.16, R25.2
unnamed: J4.1, R31.2
unnamed: J4.2, R30.2
unnamed: J4.8, R27.2
unnamed: L3.1, U3.7
unnamed: L4.1, U4.7
unnamed: R6.2, U9.10
unnamed: R9.1, U9.24
unnamed: R13.1, R17.2, U9.7
unnamed: R14.1, R18.2, U9.11
unnamed: R15.1, U9.14
unnamed: R7.1, R16.2, U9.8
VBUS: C42.1, J1.A4, J1.A9, J1.B4, J1.B9, U5.1, U5.3, U12.1
VDDA: C7.1, C8.1, L1.2, U1.32, U1.33

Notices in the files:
PCBs/h730duino_h730duino/processed.kicad_pcb:
MIT License
Copyright © 2021
parts and their libraries:
Copyright 2016 Accelerated Designs. All rights reserved.
